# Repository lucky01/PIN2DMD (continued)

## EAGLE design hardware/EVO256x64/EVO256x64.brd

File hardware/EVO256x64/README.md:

# PIN2DMD EVO256x64

The files are provided as is for unmodified production use only.
Any modification without written approval is forbidden.

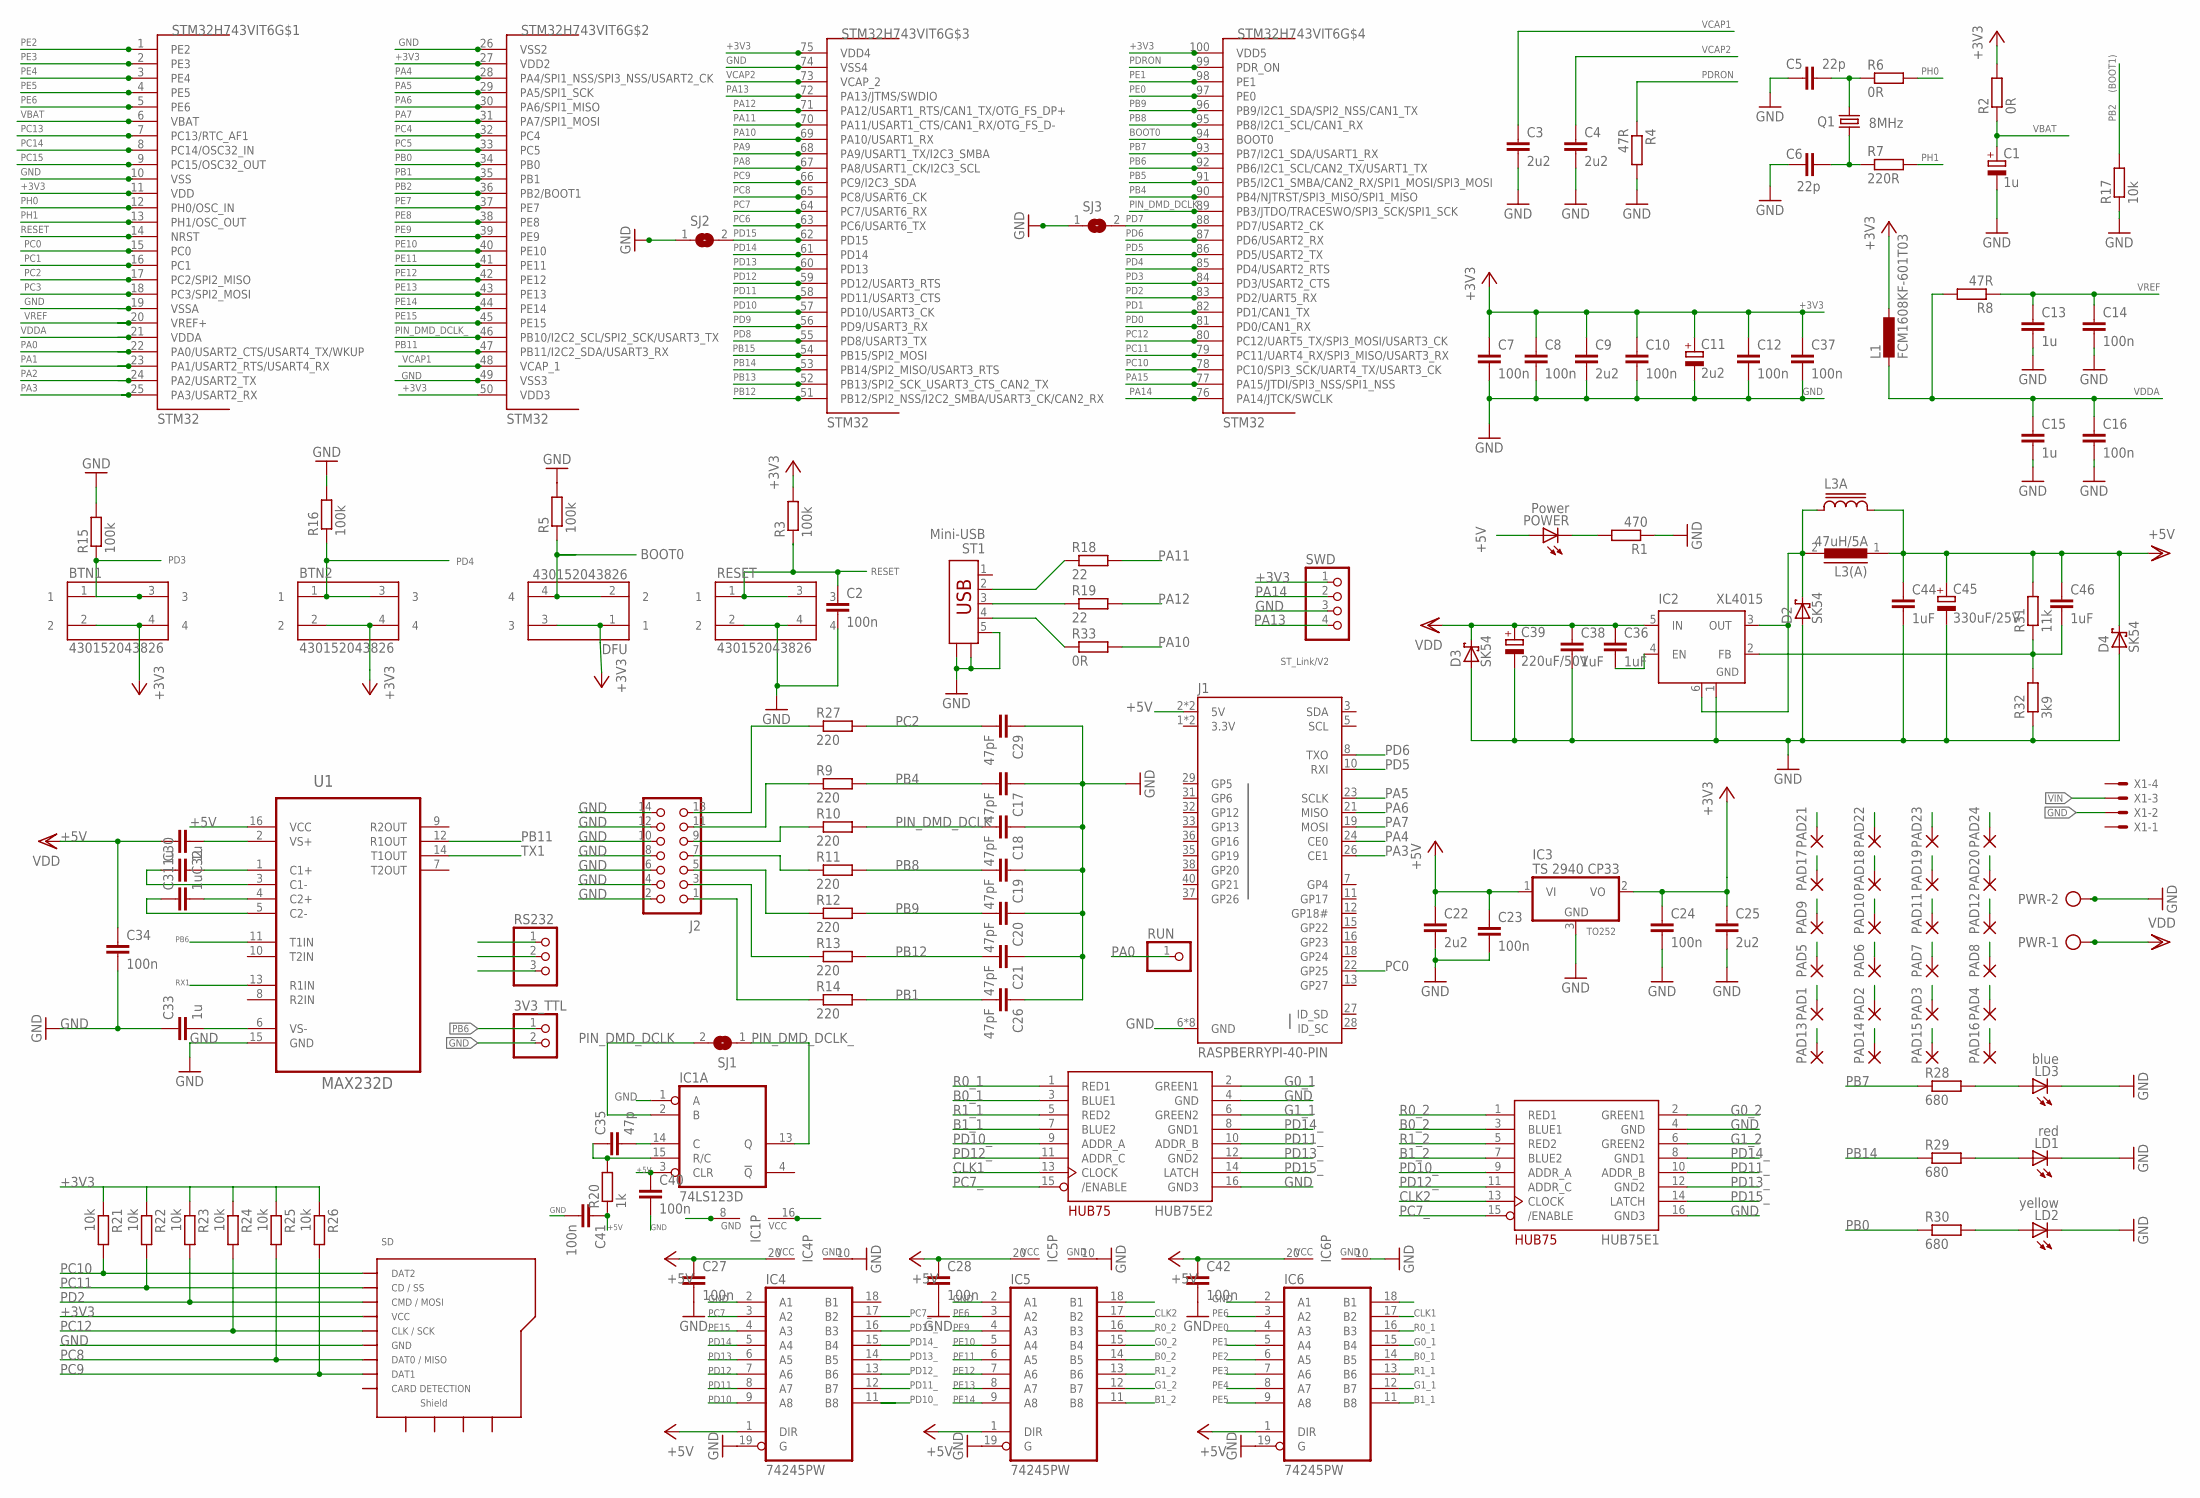
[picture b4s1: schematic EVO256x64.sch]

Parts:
3V3_TTL: PINHD-1X2; 1X02
BTN1, BTN2: 430152043826
C1: 1u; CT3528
C2, C7, C8, C10, C12, C14, C16, C23, C24, C27, C28, C34, C37, C40, C41, C42: 100n; C0805
C3, C4: 2u2; C0805
C5, C6: 22p; C0805
C9, C22, C25: 2u2; C1206
C11: 2u2; CT3528
C13, C15: 1u; C1206
C17, C18, C19, C20, C21, C26, C29: 47pF; C0805
C30, C31, C32, C33: 1u; C0805
C35: 47p; C0805
C36, C38, C44, C46: 1uF; C1206
C39: 220uF/50V; PANASONIC_G
C45: 330uF/25V; PANASONIC_G
D2, D3, D4: SK54; SMB
DFU: 430152043826
HUB75E1, HUB75E2: RGB; 2X08-IDC
IC1: 74LS123D; SO16
IC2: XL4015; TO263-5
IC3: TS 2940 CP33; TO252
IC4, IC5, IC6: 74245PW; TSSOP20
J1: RASPBERRYPI-40-PIN; 2X20
J2: CON_HEADER_2X07-PTH-SHROUDED; PINSHRD_PTH_2X07
L1: FCM1608KF-601T03; L2012C
L3(A): 47uH/5A; ED16
L3A: SRR1206
LD1: red; CHIP-LED0805
LD2: yellow; CHIP-LED0805
LD3: blue; CHIP-LED0805
PAD1, PAD2, PAD3, PAD4, PAD5, PAD6, PAD7, PAD8, PAD9, PAD10, PAD11, PAD12, PAD13, PAD14, PAD15, PAD16, PAD17, PAD18, PAD19, PAD20, PAD21, PAD22, PAD23, PAD24: SMD5; SMD2,54-5,08
POWER: Power; CHIPLED_0805
PWR: AK500/2-H
Q1: 8MHz; HC49UP
R1: 470; R0805
R2, R6, R33: 0R; R0805
R3, R5, R15, R16: 100k; R0805
R4, R8: 47R; R0805
R7: 220R; R0805
R9, R10, R11, R12, R13, R14, R27: 220; R0805
R17, R21, R22, R23, R24, R25, R26: 10k; R0805
R18, R19: 22; R0805
R20: 1k; R0805
R28, R29, R30: 680; R0805
R31: 11k; R1206
R32: 3k9; R1206
RESET: 430152043826
RS232: PINHD-1X3; 1X03
RUN: PINHD-1X1; 1X01
SD: MICROSD_CARD_POLLIN; MR**-AP*03**
SJ1, SJ2, SJ3: SJ
ST1: Mini-USB; USBMINI
STM32H743VIT6: STM32; LQFP100
SWD: PINHD-1X4; 1X04
U1: MAX232D; SOIC127P600X175-16N
X1: KK-156-4

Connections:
3.3V: J1.1 (3.3V), J1.17 (3.3V)
+3V3: BTN1.2, BTN1.4, BTN2.2, BTN2.4, C7.1, C8.1, C9.1, C10.1, C11.+, C12.1, C24.1, C25.1, C37.1, DFU.1, DFU.3, IC3.2 (VO), L1.1, R2.2, R3.2, R21.1, R22.1, R23.1, R24.1, R25.1, R26.1, SD.VCC, STM32H743VIT6.11 (VDD), STM32H743VIT6.27 (VDD2), STM32H743VIT6.50 (VDD3), STM32H743VIT6.75 (VDD4), STM32H743VIT6.100 (VDD5), SWD.1
+5V: C22.1, C23.1, C27.1, C28.1, C32.2, C34.1, C40.1, C41.1, C42.1, C44.1, C45.+, C46.1, D4.C, IC1.3 (CLR), IC1.16 (VCC), IC3.1 (VI), IC4.1 (DIR), IC4.20 (VCC), IC5.1 (DIR), IC5.20 (VCC), IC6.1 (DIR), IC6.20 (VCC), J1.2 (5V), J1.4 (5V), L3(A).1, L3A.2, PAD1.1, PAD2.1, PAD5.1, PAD6.1, PAD9.1, PAD10.1, PAD13.1, PAD14.1, PAD17.1, PAD18.1, PAD21.1, PAD22.1, POWER.A, R20.1, R31.2, U1.16 (VCC)
B0_1: HUB75E2.3 (BLUE1), IC6.14 (B5)
B0_2: HUB75E1.3 (BLUE1), IC5.14 (B5)
B1_1: HUB75E2.7 (BLUE2), IC6.11 (B8)
B1_2: HUB75E1.7 (BLUE2), IC5.11 (B8)
BOOT0: DFU.2, DFU.4, R5.1, STM32H743VIT6.94 (BOOT0)
CLK1: HUB75E2.13 (CLOCK), IC6.17 (B2)
CLK2: HUB75E1.13 (CLOCK), IC5.17 (B2)
G0_1: HUB75E2.2 (GREEN1), IC6.15 (B4)
G0_2: HUB75E1.2 (GREEN1), IC5.15 (B4)
G1_1: HUB75E2.6 (GREEN2), IC6.12 (B7)
G1_2: HUB75E1.6 (GREEN2), IC5.12 (B7)
GND: 3V3_TTL.2, C1.-, C2.2, C3.2, C4.2, C5.2, C6.2, C7.2, C8.2, C9.2, C10.2, C11.-, C12.2, C13.2, C14.2, C15.2, C16.2, C17.1, C18.1, C19.1, C20.1, C21.1, C22.2, C23.2, C24.2, C25.2, C26.1, C27.2, C28.2, C29.1, C33.1, C34.2, C37.2, C38.2, C39.-, C40.2, C41.2, C42.2, C44.2, C45.-, D2.A, D3.A, D4.A, HUB75E1.4 (GND), HUB75E1.16 (GND3), HUB75E2.4 (GND), HUB75E2.16 (GND3), IC1.1 (A), IC1.8 (GND), IC2.1 (GND), IC3.3 (GND), IC4.2 (A1), IC4.10 (GND), IC4.19 (G), IC5.2 (A1), IC5.10 (GND), IC5.19 (G), IC6.2 (A1), IC6.10 (GND), IC6.19 (G), J1.6 (GND), J1.9 (GND), J1.14 (GND), J1.20 (GND), J1.25 (GND), J1.30 (GND), J1.34 (GND), J1.39 (GND), J2.2, J2.4, J2.6, J2.8, J2.10, J2.12, J2.14, LD1.C, LD2.C, LD3.C, PAD3.1, PAD4.1, PAD7.1, PAD8.1, PAD11.1, PAD12.1, PAD15.1, PAD16.1, PAD19.1, PAD20.1, PAD23.1, PAD24.1, PWR.2, R1.1, R4.2, R5.2, R15.2, R16.2, R17.1, R32.1, RESET.2, RESET.4, RS232.2, SD.GND, SJ2.1, SJ3.1, ST1.5, ST1.N1, ST1.N2, STM32H743VIT6.10 (VSS), STM32H743VIT6.19 (VSSA), STM32H743VIT6.26 (VSS2), STM32H743VIT6.49 (VSS3), STM32H743VIT6.54 (PB15/SPI2_MOSI), STM32H743VIT6.74 (VSS4), SWD.3, U1.15 (GND), X1.2
unnamed: C5.1, Q1.2, R6.1
unnamed: C6.1, Q1.1, R7.1
unnamed: POWER.C, R1.2
unnamed: J2.13, R27.1
unnamed: J2.11, R9.1
unnamed: J2.9, R10.1
unnamed: J2.7, R11.1
unnamed: J2.5, R12.1
unnamed: J2.3, R13.1
unnamed: C35.1, IC1.15 (R/C), R20.2
unnamed: J2.1, R14.1
unnamed: C30.2, U1.1 (C1+)
unnamed: C30.1, U1.3 (C1-)
unnamed: C31.2, U1.4 (C2+)
unnamed: C31.1, U1.5 (C2-)
unnamed: C33.2, U1.6 (VS-)
unnamed: C32.1, U1.2 (VS+)
unnamed: LD1.A, R29.2
unnamed: D2.C, IC2.3 (OUT), IC2.6 (TAB), L3(A).2, L3A.1
unnamed: C46.2, IC2.2 (FB), R31.1, R32.2
unnamed: C35.2, IC1.14 (C)
unnamed: LD3.A, R28.2
unnamed: C36.2, IC2.4 (EN)
unnamed: R33.1, ST1.4
unnamed: LD2.A, R30.2
unnamed: R19.1, ST1.3
unnamed: R18.1, ST1.2
PA0: RUN.1, STM32H743VIT6.22 (PA0/USART2_CTS/USART4_TX/WKUP)
PA1: STM32H743VIT6.23 (PA1/USART2_RTS/USART4_RX)
PA2: STM32H743VIT6.24 (PA2/USART2_TX)
PA3: J1.26 (CE1), STM32H743VIT6.25 (PA3/USART2_RX)
PA4: J1.24 (CE0), STM32H743VIT6.28 (PA4/SPI1_NSS/SPI3_NSS/USART2_CK)
PA5: J1.23 (SCLK), STM32H743VIT6.29 (PA5/SPI1_SCK)
PA6: J1.21 (MISO), STM32H743VIT6.30 (PA6/SPI1_MISO)
PA7: J1.19 (MOSI), STM32H743VIT6.31 (PA7/SPI1_MOSI)
PA8: STM32H743VIT6.67 (PA8/USART1_CK/I2C3_SCL)
PA9: STM32H743VIT6.68 (PA9/USART1_TX/I2C3_SMBA)
PA10: R33.2, STM32H743VIT6.69 (PA10/USART1_RX)
PA11: R18.2, STM32H743VIT6.70 (PA11/USART1_CTS/CAN1_RX/OTG_FS_D-)
PA12: R19.2, STM32H743VIT6.71 (PA12/USART1_RTS/CAN1_TX/OTG_FS_DP+)
PA13: STM32H743VIT6.72 (PA13/JTMS/SWDIO), SWD.4
PA14: STM32H743VIT6.76 (PA14/JTCK/SWCLK), SWD.2
PA15: STM32H743VIT6.77 (PA15/JTDI/SPI3_NSS/SPI1_NSS)
PB0: R30.1, STM32H743VIT6.34 (PB0)
PB1: C26.2, R14.2, STM32H743VIT6.35 (PB1)
PB2: R17.2, STM32H743VIT6.36 (PB2/BOOT1)
PB4: C17.2, R9.2, STM32H743VIT6.90 (PB4/NJTRST/SPI3_MISO/SPI1_MISO)
PB5: STM32H743VIT6.91 (PB5/I2C1_SMBA/CAN2_RX/SPI1_MOSI/SPI3_MO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)
PB6: 3V3_TTL.1, STM32H743VIT6.92 (PB6/I2C1_SCL/CAN2_TX/USART1_TX), U1.11 (T1IN)
PB7: R28.1, STM32H743VIT6.93 (PB7/I2C1_SDA/USART1_RX)
PB8: C19.2, R11.2, STM32H743VIT6.95 (PB8/I2C1_SCL/CAN1_RX)
PB9: C20.2, R12.2, STM32H743VIT6.96 (PB9/I2C1_SDA/SPI2_NSS/CAN1_TX)
PB11: STM32H743VIT6.47 (PB11/I2C2_SDA/USART3_RX), U1.12 (R1OUT)
PB12: C21.2, R13.2, STM32H743VIT6.51 (PB12/SPI2_NSS/I2C2_SMBA/USART3_CK/CAN2_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)
PB13: STM32H743VIT6.52 (PB13/SPI2_SCK_USART3_CTS_CAN2_TX)
PB14: R29.1, STM32H743VIT6.53 (PB14/SPI2_MISO/USART3_RTS)
PC0: J1.22 (GP25), STM32H743VIT6.15 (PC0)
PC1: STM32H743VIT6.16 (PC1)
PC2: C29.2, R27.2, STM32H743VIT6.17 (PC2/SPI2_MISO)
PC3: STM32H743VIT6.18 (PC3/SPI2_MOSI)
PC4: STM32H743VIT6.32 (PC4)
PC5: STM32H743VIT6.33 (PC5)
PC6: STM32H743VIT6.63 (PC6/USART6_TX)
PC7: IC4.3 (A2), STM32H743VIT6.64 (PC7/USART6_RX)
PC7_: HUB75E1.15 (/ENABLE), HUB75E2.15 (/ENABLE), IC4.17 (B2)
PC8: R25.2, SD.DAT0 (DAT0/MISO), STM32H743VIT6.65 (PC8/USART6_CK)
PC9: R26.2, SD.DAT1, STM32H743VIT6.66 (PC9/I2C3_SDA)
PC10: R21.2, SD.DAT2, STM32H743VIT6.78 (PC10/SPI3_SCK/UART4_TX/USART3_CK)
PC11: R22.2, SD.DAT3/CS (CD/SS), STM32H743VIT6.79 (PC11/UART4_RX/SPI3_MISO/USART3_RX)
PC12: R24.2, SD.CLK (CLK/SCK), STM32H743VIT6.80 (PC12/UART5_TX/SPI3_MOSI/USART3_CK)
PC13: STM32H743VIT6.7 (PC13/RTC_AF1)
PC14: STM32H743VIT6.8 (PC14/OSC32_IN)
PC15: STM32H743VIT6.9 (PC15/OSC32_OUT)
PD0: STM32H743VIT6.81 (PD0/CAN1_RX)
PD1: STM32H743VIT6.82 (PD1/CAN1_TX)
PD2: R23.2, SD.CMD (CMD/MOSI), STM32H743VIT6.83 (PD2/UART5_RX)
PD3: BTN1.1, BTN1.3, R15.1, STM32H743VIT6.84 (PD3/USART2_CTS)
PD4: BTN2.1, BTN2.3, R16.1, STM32H743VIT6.85 (PD4/USART2_RTS)
PD5: J1.10 (RXI), STM32H743VIT6.86 (PD5/USART2_TX)
PD6: J1.8 (TXO), STM32H743VIT6.87 (PD6/USART2_RX)
PD7: SJ3.2, STM32H743VIT6.88 (PD7/USART2_CK)
PD8: STM32H743VIT6.55 (PD8/USART3_TX)
PD9: STM32H743VIT6.56 (PD9/USART3_RX)
PD10: IC4.9 (A8), STM32H743VIT6.57 (PD10/USART3_CK)
PD10_: HUB75E1.9 (ADDR_A), HUB75E2.9 (ADDR_A), IC4.11 (B8)
PD11: IC4.8 (A7), STM32H743VIT6.58 (PD11/USART3_CTS)
PD11_: HUB75E1.10 (ADDR_B), HUB75E2.10 (ADDR_B), IC4.12 (B7)
PD12: IC4.7 (A6), STM32H743VIT6.59 (PD12/USART3_RTS)
PD12_: HUB75E1.11 (ADDR_C), HUB75E2.11 (ADDR_C), IC4.13 (B6)
PD13: IC4.6 (A5), STM32H743VIT6.60 (PD13)
PD13_: HUB75E1.12 (GND2), HUB75E2.12 (GND2), IC4.14 (B5)
PD14: IC4.5 (A4), STM32H743VIT6.61 (PD14)
PD14_: HUB75E1.8 (GND1), HUB75E2.8 (GND1), IC4.15 (B4)
PD15: SJ2.2, STM32H743VIT6.62 (PD15)
PD15_: HUB75E1.14 (LATCH), HUB75E2.14 (LATCH), IC4.16 (B3)
PDRON: R4.1, STM32H743VIT6.99 (PDR_ON)
PE0: IC6.4 (A3), STM32H743VIT6.97 (PE0)
PE1: IC6.5 (A4), STM32H743VIT6.98 (PE1)
PE2: IC6.6 (A5), STM32H743VIT6.1 (PE2)
PE3: IC6.7 (A6), STM32H743VIT6.2 (PE3)
PE4: IC6.8 (A7), STM32H743VIT6.3 (PE4)
PE5: IC6.9 (A8), STM32H743VIT6.4 (PE5)
PE6: IC5.3 (A2), IC6.3 (A2), STM32H743VIT6.5 (PE6)
PE7: STM32H743VIT6.37 (PE7)
PE8: STM32H743VIT6.38 (PE8)
PE9: IC5.4 (A3), STM32H743VIT6.39 (PE9)
PE10: IC5.5 (A4), STM32H743VIT6.40 (PE10)
PE11: IC5.6 (A5), STM32H743VIT6.41 (PE11)
PE12: IC5.7 (A6), STM32H743VIT6.42 (PE12)
PE13: IC5.8 (A7), STM32H743VIT6.43 (PE13)
PE14: IC5.9 (A8), STM32H743VIT6.44 (PE14)
PE15: IC4.4 (A3), STM32H743VIT6.45 (PE15)
PH0: R6.2, STM32H743VIT6.12 (PH0/OSC_IN)
PH1: R7.2, STM32H743VIT6.13 (PH1/OSC_OUT)
PIN_DMD_DCLK: C18.2, IC1.2 (B), R10.2, SJ1.2
PIN_DMD_DCLK_: IC1.13 (Q), SJ1.1, STM32H743VIT6.46 (PB10/I2C2_SCL/SPI2_SCK/USART3_TX), STM32H743VIT6.89 (PB3/JTDO/TRACESWO/SPI3_SCK/SPI1_SCK)
R0_1: HUB75E2.1 (RED1), IC6.16 (B3)
R0_2: HUB75E1.1 (RED1), IC5.16 (B3)
R1_1: HUB75E2.5 (RED2), IC6.13 (B6)
R1_2: HUB75E1.5 (RED2), IC5.13 (B6)
RESET: C2.1, R3.1, RESET.1, RESET.3, STM32H743VIT6.14 (NRST)
RX1: RS232.3, U1.13 (R1IN)
TX1: RS232.1, U1.14 (T1OUT)
VBAT: C1.+, R2.1, STM32H743VIT6.6 (VBAT)
VCAP1: C3.1, STM32H743VIT6.48 (VCAP_1)
VCAP2: C4.1, STM32H743VIT6.73 (VCAP_2)
VDDA: C15.1, C16.1, L1.2, R8.2, STM32H743VIT6.21 (VDDA)
VIN: C36.1, C38.1, C39.+, D3.C, IC2.5 (IN), PWR.1, X1.3
VREF: C13.1, C14.1, R8.1, STM32H743VIT6.20 (VREF+)

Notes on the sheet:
TO252
(BOOT1)
ST_Link/V2
PB15

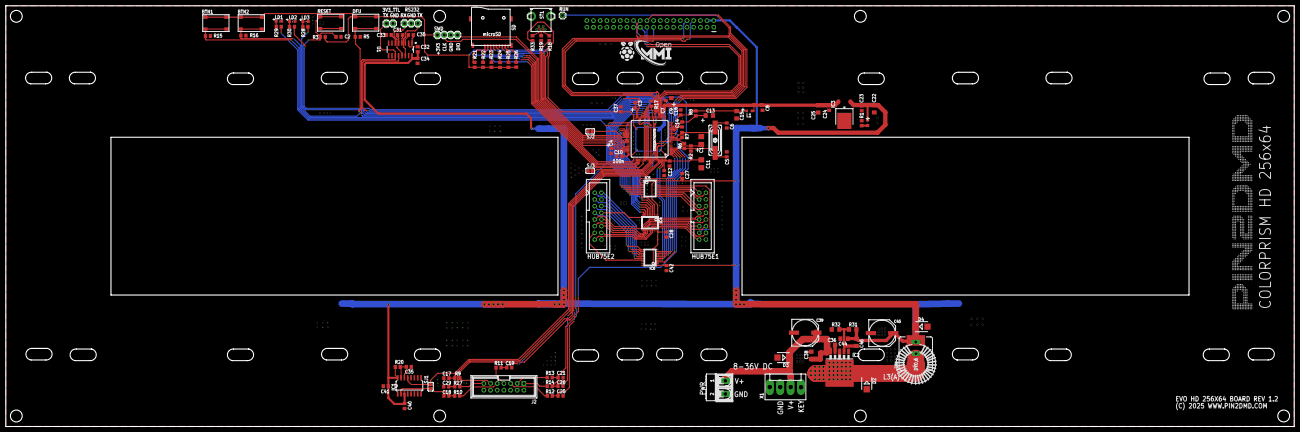
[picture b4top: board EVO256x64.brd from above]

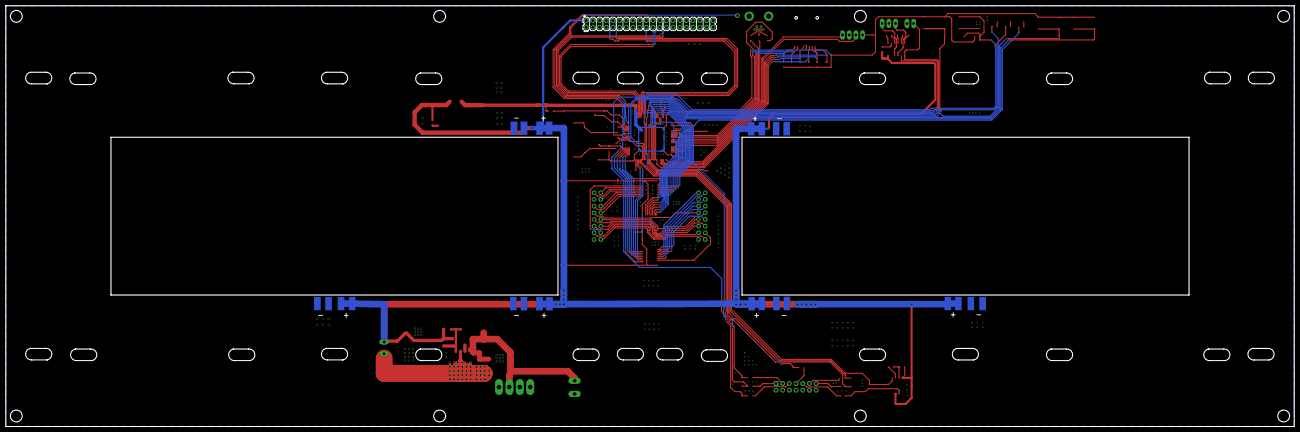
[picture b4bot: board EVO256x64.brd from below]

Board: 2 copper layers, 490.0 x 160.0 mm, 140 parts (25 on the bottom side), 123 nets.

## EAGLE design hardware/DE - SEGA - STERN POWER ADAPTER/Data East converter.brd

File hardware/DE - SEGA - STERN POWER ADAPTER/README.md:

# DATAEAST POWER ADAPTER BOARD

This are the PCB files for a power adapter which can be plugged in the powerdriver board of DE version 3 / Sega version 3 & Whitestar / Stern Whitestar & S.A.M.
machines. PCB design by Rene Venema

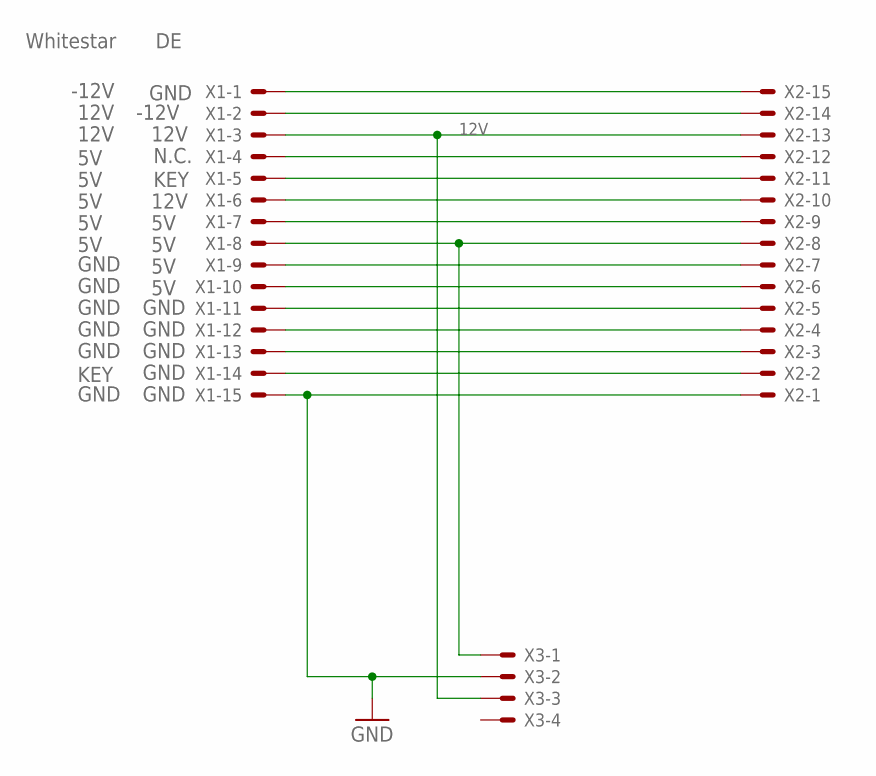
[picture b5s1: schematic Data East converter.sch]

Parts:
X1: KK-156-15_FKK-156-15-F; KK-156-15_F
X2: KK-156-15
X3: KK-156-4

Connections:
12V: X1.3, X2.13, X3.3
GND: X1.15, X2.1, X3.2
unnamed: X1.14, X2.2
unnamed: X1.10, X2.6
unnamed: X1.2, X2.14
unnamed: X1.1, X2.15
unnamed: X1.4, X2.12
unnamed: X1.6, X2.10
unnamed: X1.8, X2.8, X3.1
unnamed: X1.7, X2.9
unnamed: X1.9, X2.7
unnamed: X1.5, X2.11
unnamed: X1.13, X2.3
unnamed: X1.12, X2.4
unnamed: X1.11, X2.5

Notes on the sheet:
12V
GND
-12V
N.C.
KEY
Whitestar

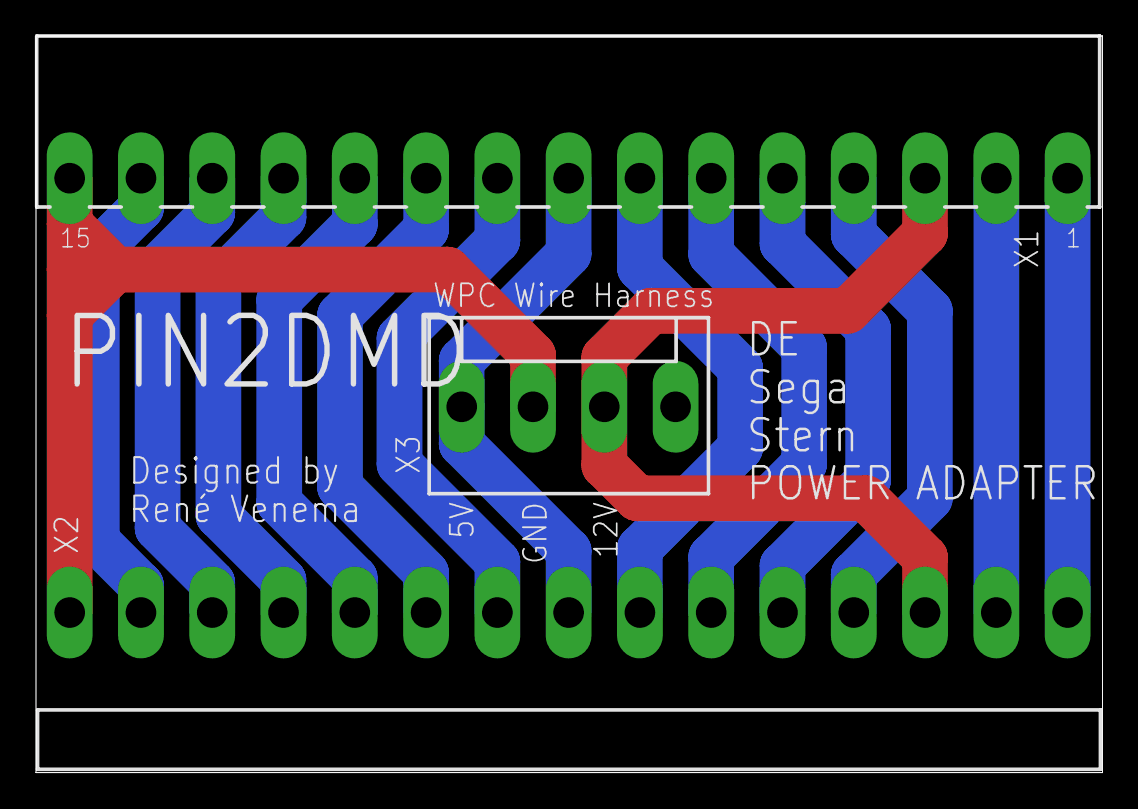
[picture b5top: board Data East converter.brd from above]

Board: 2 copper layers, 59.2 x 40.9 mm, 3 parts (0 on the bottom side), 15 nets.

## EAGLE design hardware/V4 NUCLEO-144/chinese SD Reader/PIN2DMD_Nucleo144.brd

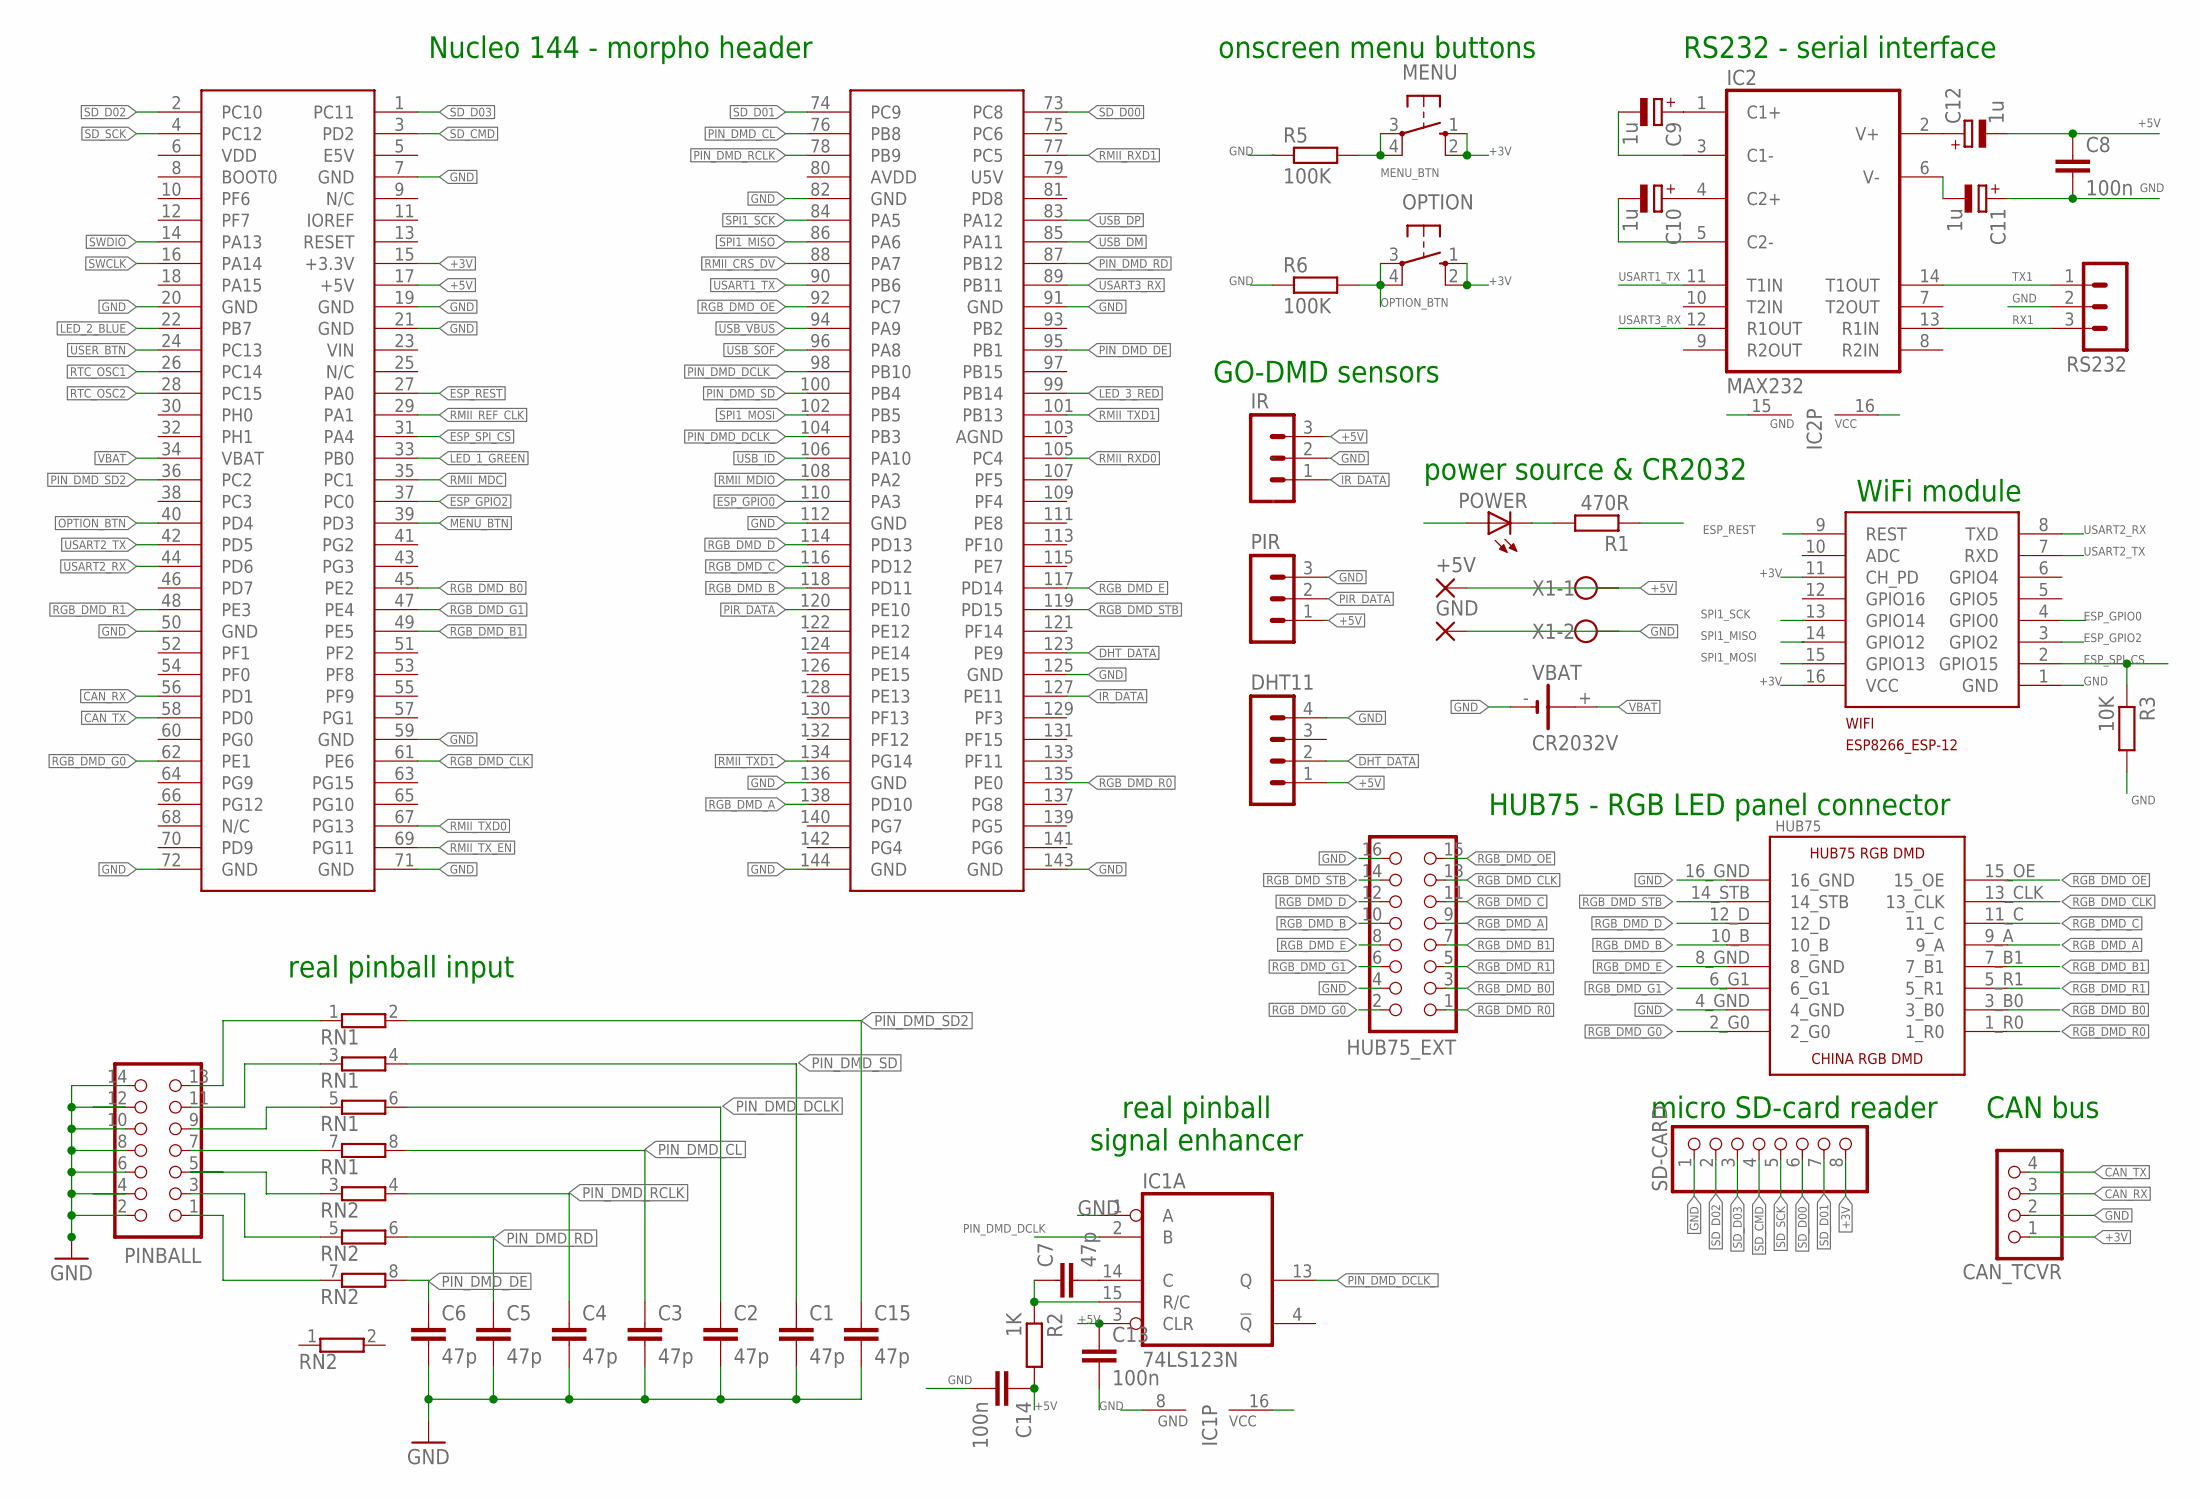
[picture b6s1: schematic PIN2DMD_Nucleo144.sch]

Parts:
+5V: WIREPADSMD2,54-5,08; SMD2,54-5,08
C1, C2, C3, C4, C5, C6, C7, C15: 47p; C025-024X044
C8, C13, C14: 100n; C025-024X044
C9, C10, C11, C12: 1u; E2-4
CAN_TCVR: PINHD-1X4; 1X04
DHT11: MA04-1
GND: WIREPADSMD2,54-5,08; SMD2,54-5,08
HUB75: RGB_DMD_HUB75_HEADER_FEMALE; 16_PIN_HUB75_RGB_FEMALE_DOWN
HUB75_EXT: CON_HEADER_2X08B; PINSHRD_PTH_2X08
IC1: 74LS123N; DIL16
IC2: MAX232; DIL16
IR: MA03-1
MENU: 10-XX; B3F-10XX
OPTION: 10-XX; B3F-10XX
PINBALL: CON_HEADER_2X07-PTH-SHROUDED; PINSHRD_PTH_2X07
PIR: MA03-1
POWER: LED3MM
R1: 470R; 0207/10
R2: 1K; 0207/10
R3: 10K; 0207/10
R5, R6: 100K; 0207/10
RN1, RN2: E4RP; SIL8
RS232: MA03-1
SD-CARD: PINHD-1X8; 1X08
U$1: NUCLEO-144
VBAT: CR2032V
WIFI: ESP8266_ESP-12; ESP8266-ESP12
X1: W237-102

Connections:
+3V: CAN_TCVR.1, MENU.1 (S), MENU.2 (S1), OPTION.1 (S), OPTION.2 (S1), SD-CARD.8, U$1.15 (+3.3V), WIFI.11 (CH_PD), WIFI.16 (VCC)
+5V: +5V.1, C8.1, C12.-, C13.1, C14.1, DHT11.1, IC1.3 (CLR), IC1.16 (VCC), IC2.16 (VCC), IR.3, PIR.1, POWER.A, R2.2, U$1.17 (+5V), X1.1
CAN_RX: CAN_TCVR.3, U$1.56 (PD1)
CAN_TX: CAN_TCVR.4, U$1.58 (PD0)
DHT_DATA: DHT11.2, U$1.123 (PE9)
ESP_GPIO0: U$1.110 (PA3), WIFI.4 (GPIO0)
ESP_GPIO2: U$1.37 (PC0), WIFI.3 (GPIO2)
ESP_REST: U$1.27 (PA0), WIFI.9 (REST)
ESP_SPI_CS: R3.1, U$1.31 (PA4), WIFI.2 (GPIO15)
GND: C1.2, C2.2, C3.2, C4.2, C5.2, C6.2, C8.2, C11.+, C13.2, C14.2, C15.2, CAN_TCVR.2, DHT11.4, GND.1, HUB75.4_GND, HUB75.16_GND, HUB75_EXT.4, HUB75_EXT.16, IC1.1 (A), IC1.8 (GND), IC2.15 (GND), IR.2, PINBALL.2, PINBALL.4, PINBALL.6, PINBALL.8, PINBALL.10, PINBALL.12, PINBALL.14, PIR.3, R1.1, R3.2, R5.1, R6.1, RS232.2, SD-CARD.1, U$1.7 (GND), U$1.19 (GND), U$1.20 (GND), U$1.21 (GND), U$1.50 (GND), U$1.59 (GND), U$1.71 (GND), U$1.72 (GND), U$1.82 (GND), U$1.91 (GND), U$1.112 (GND), U$1.125 (GND), U$1.136 (GND), U$1.143 (GND), U$1.144 (GND), VBAT.-, WIFI.1 (GND), X1.2
IR_DATA: IR.1, U$1.127 (PE11)
LED_1_GREEN: U$1.33 (PB0)
LED_2_BLUE: U$1.22 (PB7)
LED_3_RED: U$1.99 (PB14)
MENU_BTN: MENU.3, MENU.4 (P1), R5.2, U$1.39 (PD3)
unnamed: POWER.K (C), R1.2
unnamed: C7.1, IC1.15 (R/C), R2.1
unnamed: C7.2, IC1.14 (C)
unnamed: C9.+, IC2.1 (C1+)
unnamed: PINBALL.7, RN1.7 (1)
unnamed: PINBALL.5, RN2.3 (1)
unnamed: C10.+, IC2.4 (C2+)
unnamed: C11.-, IC2.6 (V-)
unnamed: C9.-, IC2.3 (C1-)
unnamed: C10.-, IC2.5 (C2-)
unnamed: PINBALL.3, RN2.5 (1)
unnamed: PINBALL.1, RN2.7 (1)
unnamed: PINBALL.9, RN1.5 (1)
unnamed: PINBALL.11, RN1.3 (1)
unnamed: C12.+, IC2.2 (V+)
unnamed: PINBALL.13, RN1.1
OPTION_BTN: OPTION.3, OPTION.4 (P1), R6.2, U$1.40 (PD4)
PIN_DMD_CL: C3.1, RN1.8 (2), U$1.76 (PB8)
PIN_DMD_DCLK: C2.1, IC1.2 (B), RN1.6 (2)
PIN_DMD_DCLK_: IC1.13 (Q), U$1.98 (PB10), U$1.104 (PB3)
PIN_DMD_DE: C6.1, RN2.8 (2), U$1.95 (PB1)
PIN_DMD_RCLK: C4.1, RN2.4 (2), U$1.78 (PB9)
PIN_DMD_RD: C5.1, RN2.6 (2), U$1.87 (PB12)
PIN_DMD_SD: C1.1, RN1.4 (2), U$1.100 (PB4)
PIN_DMD_SD2: C15.1, RN1.2, U$1.36 (PC2)
PIR_DATA: PIR.2, U$1.120 (PE10)
RGB_DMD_A: HUB75.9_A, HUB75_EXT.9, U$1.138 (PD10)
RGB_DMD_B: HUB75.10_B, HUB75_EXT.10, U$1.118 (PD11)
RGB_DMD_B0: HUB75.3_B0, HUB75_EXT.3, U$1.45 (PE2)
RGB_DMD_B1: HUB75.7_B1, HUB75_EXT.7, U$1.49 (PE5)
RGB_DMD_C: HUB75.11_C, HUB75_EXT.11, U$1.116 (PD12)
RGB_DMD_CLK: HUB75.13_CLK, HUB75_EXT.13, U$1.61 (PE6)
RGB_DMD_D: HUB75.12_D, HUB75_EXT.12, U$1.114 (PD13)
RGB_DMD_E: HUB75.8_GND, HUB75_EXT.8, U$1.117 (PD14)
RGB_DMD_G0: HUB75.2_G0, HUB75_EXT.2, U$1.62 (PE1)
RGB_DMD_G1: HUB75.6_G1, HUB75_EXT.6, U$1.47 (PE4)
RGB_DMD_OE: HUB75.15_OE, HUB75_EXT.15, U$1.92 (PC7)
RGB_DMD_R0: HUB75.1_R0, HUB75_EXT.1, U$1.135 (PE0)
RGB_DMD_R1: HUB75.5_R1, HUB75_EXT.5, U$1.48 (PE3)
RGB_DMD_STB: HUB75.14_STB, HUB75_EXT.14, U$1.119 (PD15)
RMII_CRS_DV: U$1.88 (PA7)
RMII_MDC: U$1.35 (PC1)
RMII_MDIO: U$1.108 (PA2)
RMII_REF_CLK: U$1.29 (PA1)
RMII_RXD0: U$1.105 (PC4)
RMII_RXD1: U$1.77 (PC5)
RMII_TXD0: U$1.67 (PG13)
RMII_TXD1: U$1.101 (PB13), U$1.134 (PG14)
RMII_TX_EN: U$1.69 (PG11)
RTC_OSC1: U$1.26 (PC14)
RTC_OSC2: U$1.28 (PC15)
RX1: IC2.13 (R1IN), RS232.3
SD_CMD: SD-CARD.4, U$1.3 (PD2)
SD_D00: SD-CARD.6, U$1.73 (PC8)
SD_D01: SD-CARD.7, U$1.74 (PC9)
SD_D02: SD-CARD.2, U$1.2 (PC10)
SD_D03: SD-CARD.3, U$1.1 (PC11)
SD_SCK: SD-CARD.5, U$1.4 (PC12)
SPI1_MISO: U$1.86 (PA6), WIFI.14 (GPIO12)
SPI1_MOSI: U$1.102 (PB5), WIFI.15 (GPIO13)
SPI1_SCK: U$1.84 (PA5), WIFI.13 (GPIO14)
SWCLK: U$1.16 (PA14)
SWDIO: U$1.14 (PA13)
TX1: IC2.14 (T1OUT), RS232.1
USART1_TX: IC2.11 (T1IN), U$1.90 (PB6)
USART2_RX: U$1.44 (PD6), WIFI.8 (TXD)
USART2_TX: U$1.42 (PD5), WIFI.7 (RXD)
USART3_RX: IC2.12 (R1OUT), U$1.89 (PB11)
USB_DM: U$1.85 (PA11)
USB_DP: U$1.83 (PA12)
USB_ID: U$1.106 (PA10)
USB_SOF: U$1.96 (PA8)
USB_VBUS: U$1.94 (PA9)
USER_BTN: U$1.24 (PC13)
VBAT: U$1.34 (VBAT), VBAT.+

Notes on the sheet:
power source & CR2032
onscreen menu buttons
WiFi module
Nucleo 144 - morpho header
HUB75 - RGB LED panel connector
RS232 - serial interface
GO-DMD sensors
CAN bus
micro SD-card reader
real pinball input
real pinball signal enhancer

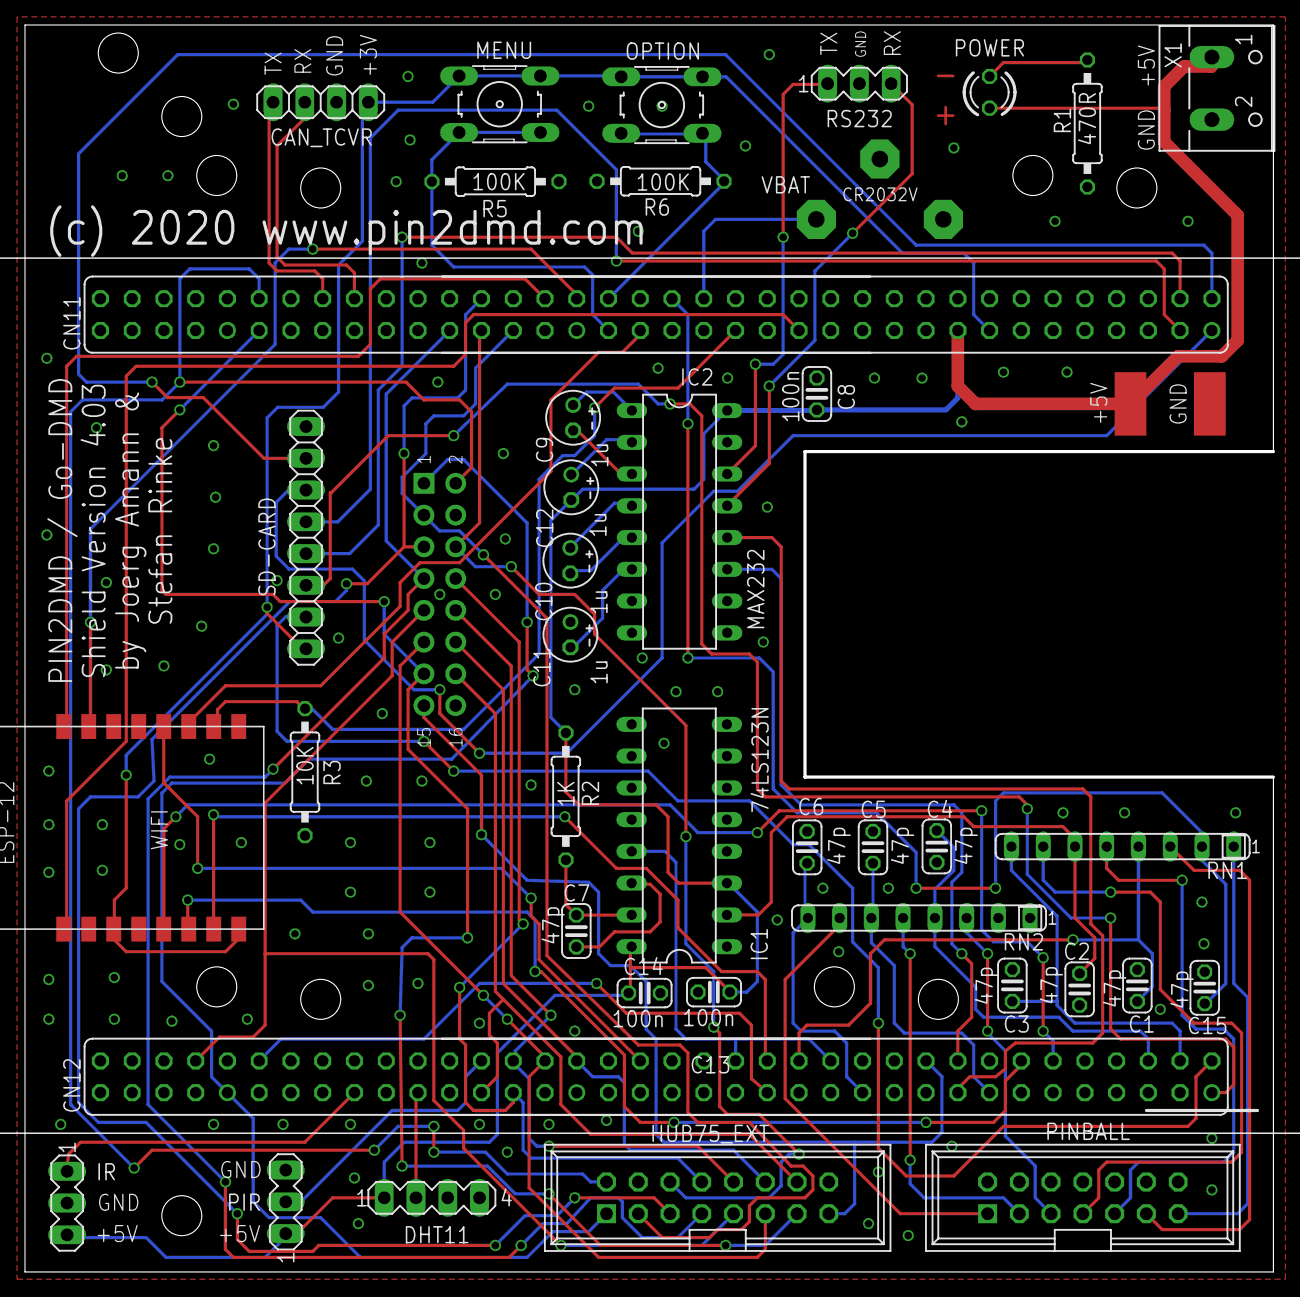
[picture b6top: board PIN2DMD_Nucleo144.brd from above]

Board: 2 copper layers, 99.9 x 99.7 mm, 42 parts (1 on the bottom side), 69 nets.
